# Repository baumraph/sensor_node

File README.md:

# sensor_node
## Warning: This board has not been tested yet.

The sensor node is a board for low power wireless sensor networks.
It contains three circuits:

  1. ATMEGA328P-AU (similar circuit to an Arduino Pro Mini)
  2. NCP1402 for stepping up the voltage, which makes it possible to use only one battery.
  3. NRF24L01+ 2.4 GHz RF with external antenna
  
It is also possible to measure the voltage of the battery using pin A0.

Since the board has a similar layout as an Arduino Pro Mini, the Arduino IDE can be used to program the board.
A common library (e.g. RF24NETWORK) can be used for the software side.

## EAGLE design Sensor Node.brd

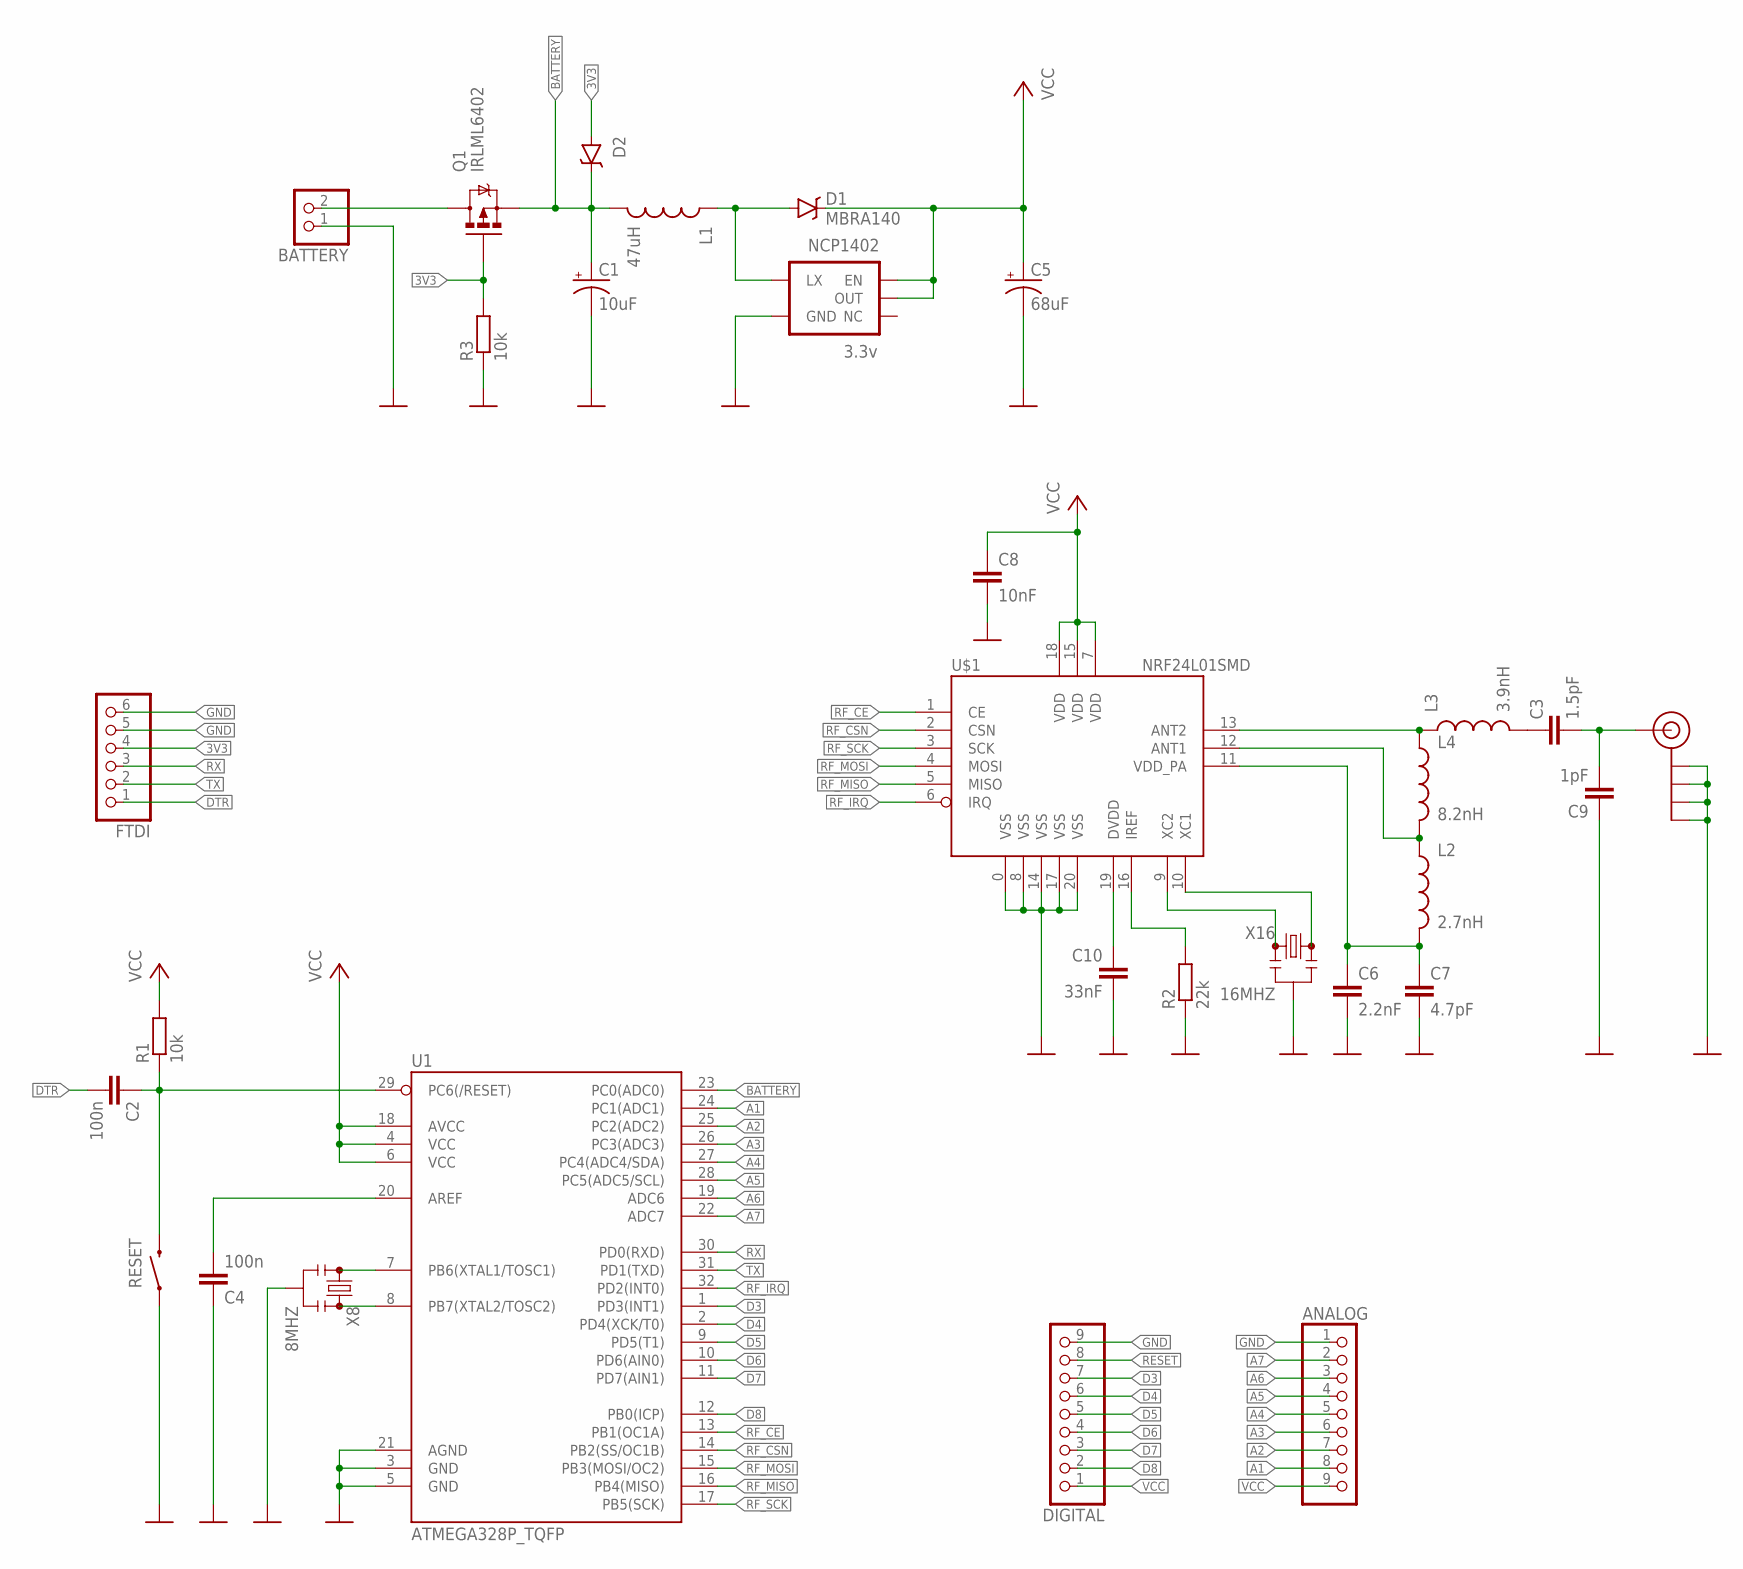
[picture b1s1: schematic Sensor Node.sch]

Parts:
ANALOG: PINHD-1X9; 1X09
BATTERY: PINHD-1X2; 1X02
C1: 10uF; EIA3216-KIT
C2, C4: 100n; C0402
C3: 1.5pF; C0402
C5: 68uF; EIA3528-KIT
C6: 2.2nF; C0402
C7: 4.7pF; C0402
C8: 10nF; C0402
C9: 1pF; C0402
C10: 33nF; C0402
D1, D2: MBRA140; SMA-DIODE
DIGITAL: PINHD-1X9; 1X09
FTDI: PINHD-1X6; 1X06
J$1: SMA_EDGE; SMA-EDGE
L1: 47uH; CR54
L2: 2.7nH; C0402
L3: 3.9nH; C0402
L4: 8.2nH; C0402
NCP1402: 3.3v; SOT23-5
Q1: IRLML6402; SOT23-3
R1, R3: 10k; R0402
R2: 22k; R0402
RESET: SWITCH-MOMENTARY-2SMD-1101NE; TACTILE-SWITCH-1101NE
U1: ATMEGA328P_TQFP; TQFP32-08
U$1: NRF24L01SMD; QFN20
X8: 8MHZ; RESONATOR-SMD
X16: 16MHZ; RESONATOR-SMD

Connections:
3V3: D2.A, FTDI.4, Q1.1 (G), R3.2
A1: ANALOG.8, U1.24 (PC1(ADC1))
A2: ANALOG.7, U1.25 (PC2(ADC2))
A3: ANALOG.6, U1.26 (PC3(ADC3))
A4: ANALOG.5, U1.27 (PC4(ADC4/SDA))
A5: ANALOG.4, U1.28 (PC5(ADC5/SCL))
A6: ANALOG.3, U1.19 (ADC6)
A7: ANALOG.2, U1.22 (ADC7)
BAT+: BATTERY.2, Q1.3 (D)
BATTERY: C1.A (+), D2.C, L1.P$2 (2), Q1.2 (S), U1.23 (PC0(ADC0))
D3: DIGITAL.7, U1.1 (PD3(INT1))
D4: DIGITAL.6, U1.2 (PD4(XCK/T0))
D5: DIGITAL.5, U1.9 (PD5(T1))
D6: DIGITAL.4, U1.10 (PD6(AIN0))
D7: DIGITAL.3, U1.11 (PD7(AIN1))
D8: DIGITAL.2, U1.12 (PB0(ICP))
DTR: C2.2, FTDI.1
GND: ANALOG.1, BATTERY.1, C1.C (-), C4.1, C5.C (-), C6.2, C7.2, C8.2, C9.1, C10.2, DIGITAL.9, FTDI.5, FTDI.6, J$1.GND@0 (GND), J$1.GND@1 (GND), J$1.GND@2 (GND), J$1.GND@3 (GND), NCP1402.4 (GND), R2.1, R3.1, RESET.1, U1.3 (GND), U1.5 (GND), U1.21 (AGND), U$1.0 (VSS), U$1.8 (VSS), U$1.14 (VSS), U$1.17 (VSS), U$1.20 (VSS), X8.2, X16.2
unnamed: D1.A, L1.P$1 (1), NCP1402.5 (LX)
unnamed: C3.1, L3.2
unnamed: C4.2, U1.20 (AREF)
unnamed: L3.1, L4.1, U$1.13 (ANT2)
unnamed: U1.7 (PB6(XTAL1/TOSC1)), X8.1
unnamed: U1.8 (PB7(XTAL2/TOSC2)), X8.3
unnamed: L2.1, L4.2, U$1.12 (ANT1)
unnamed: R2.2, U$1.16 (IREF)
unnamed: C3.2, C9.2, J$1.SIG (SIGNAL)
unnamed: C10.1, U$1.19 (DVDD)
unnamed: C6.1, C7.1, L2.2, U$1.11 (VDD_PA)
unnamed: U$1.9 (XC2), X16.3
unnamed: U$1.10 (XC1), X16.1
RESET: C2.1, DIGITAL.8, R1.1, RESET.2, U1.29 (PC6(/RESET))
RF_CE: U1.13 (PB1(OC1A)), U$1.1 (CE)
RF_CSN: U1.14 (PB2(SS/OC1B)), U$1.2 (CSN)
RF_IRQ: U1.32 (PD2(INT0)), U$1.6 (IRQ)
RF_MISO: U1.16 (PB4(MISO)), U$1.5 (MISO)
RF_MOSI: U1.15 (PB3(MOSI/OC2)), U$1.4 (MOSI)
RF_SCK: U1.17 (PB5(SCK)), U$1.3 (SCK)
RX: FTDI.3, U1.30 (PD0(RXD))
TX: FTDI.2, U1.31 (PD1(TXD))
VCC: ANALOG.9, C5.A (+), C8.1, D1.C, DIGITAL.1, NCP1402.1 (EN), NCP1402.2 (OUT), R1.2, U1.4 (VCC), U1.6 (VCC), U1.18 (AVCC), U$1.7 (VDD), U$1.15 (VDD), U$1.18 (VDD)

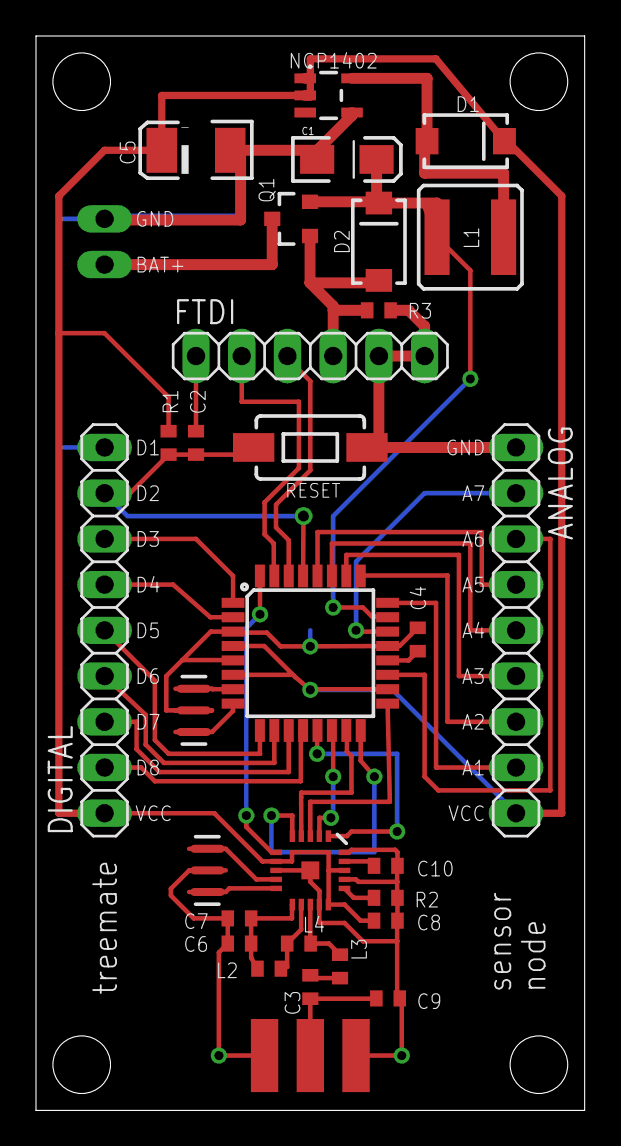
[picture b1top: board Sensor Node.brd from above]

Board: 2 copper layers, 30.5 x 59.7 mm, 31 parts (1 on the bottom side), 41 nets.

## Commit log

2016-10-13 Initial commit
    Add schematic and board
2016-10-14 Distance optimization
    Reduce the distance between the RF components
    Make vias round
2016-10-15 Refactoring
    Replace the FTDI pinheader
    Remove unwanted text
    Move and resize text

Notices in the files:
parts and their libraries:
SparkFun-DiscreteSemi: Licensing: Creative Commons ShareAlike 4.0 International - https://creativecommons.org/licenses/by-sa/4.0
